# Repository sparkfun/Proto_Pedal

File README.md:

SparkFun Proto Pedal
========================================

[*SparkFun Proto Pedal*](https://www.sparkfun.com/products/13124)

[*SparkFun Proto Pedal Chassis*](https://www.sparkfun.com/products/13967)

The SparkFun Proto Pedal is breatboard featuring prewired I/O boilerplate for building guitar stompboxes.  We also offer a matching predrilled chassis.

_**If you're looking for the Teensy Project Sketches**_ [they're here](https://github.com/sparkfun/Proto_Pedal/tree/master/projects/teensy-based).  Please remember to check the individual sketches for further notes and details in their respective `README.md` files.

Repository Contents
-------------------

* **/Hardware** - Eagle design files (.brd, .sch)
* **/Mechanical** - Enclosure files and related information
* **/Production** - Production panel files (.brd)
* **/Projects** - Example circuits build on the Proto Pedal <PRODUCT NAME>

Documentation
--------------
* **[Proto Pedal Assembly and Theory Guide](https://learn.sparkfun.com/tutorials/proto-pedal-assembly-and-theory-guide)** - Information to help get started.
* **[Chassis Hookup Guide](https://learn.sparkfun.com/tutorials/proto-pedal-chassis-hookup-guide)** - Drilling and painting the enclosure.
* **[Analog Equalizer Project](https://learn.sparkfun.com/tutorials/proto-pedal-example-analog-equalizer-project)** - the gyrator based two-band EQ example.
* **[Teensy-Audio based Programmable Digital Pedal](https://learn.sparkfun.com/tutorials/proto-pedal-example-programmable-digital-pedal)** - building a DSP development platform

Product Versions
----------------
* [SparkFun Proto Pedal](https://www.sparkfun.com/products/13124)
* [SparkFun Proto Pedal Chassis](https://www.sparkfun.com/products/13967)

Version History
---------------
* [441c191](https://github.com/sparkfun/Proto_Pedal/commit/441c1917a6b56c2a821627207be28ff88913c089) - Initial Release

License Information
-------------------

This product is _**open source**_!

Please review the LICENSE.md file for license information.

If you have any questions or concerns on licensing, please contact techsupport@sparkfun.com.

Distributed as-is; no warranty is given.

- Your friends at SparkFun.

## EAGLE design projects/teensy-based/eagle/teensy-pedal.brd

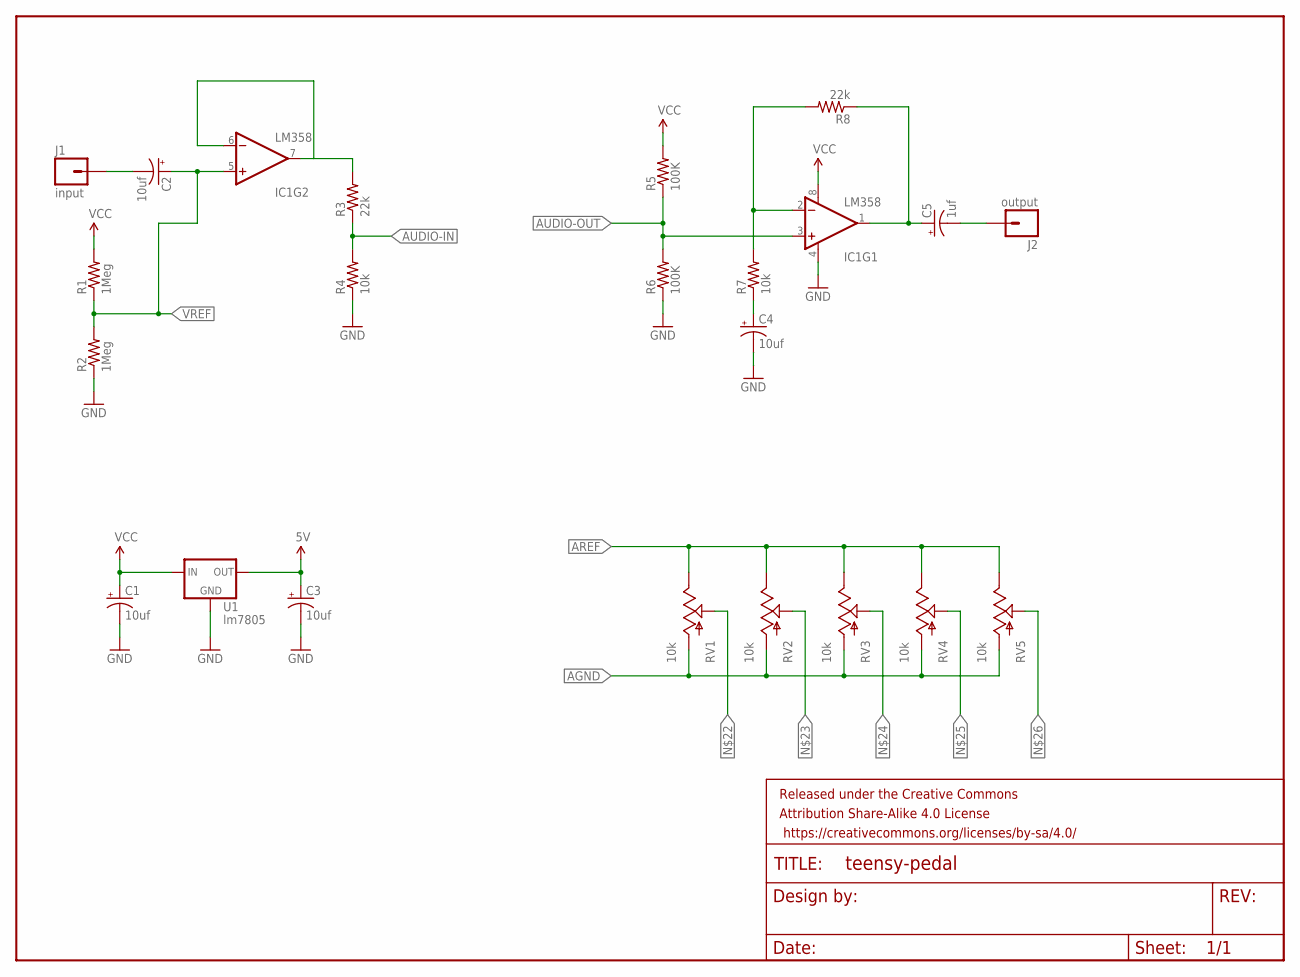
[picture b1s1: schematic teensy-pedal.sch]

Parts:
C1, C2, C3, C4: 10uf; CPOL-RADIAL-10UF-25V
C5: 1uf; CPOL-RADIAL-10UF-25V
FRAME1: FRAME-LETTER; CREATIVE_COMMONS
IC1: LM358; DIP08
J1: input; 1X01NS-KIT
J2: output; 1X01NS-KIT
R1, R2: 1Meg; AXIAL-0.3
R3, R8: 22k; AXIAL-0.3
R4, R7: 10k; AXIAL-0.3
R5, R6: 100K; AXIAL-0.3
RV1, RV2, RV3, RV4, RV5: 10k; POT_ALPHA_RV16AF-20
U1: lm7805; TO-220-ALT

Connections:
5V: C3.1 (+), U1.OUT
AGND: RV1.1 (A), RV2.1 (A), RV3.1 (A), RV4.1 (A), RV5.1 (A)
AREF: RV1.3 (E), RV2.3 (E), RV3.3 (E), RV4.3 (E), RV5.3 (E)
AUDIO-IN: R3.P$1 (1), R4.P$2 (2)
AUDIO-OUT: IC1.3 (+IN), R5.P$1 (1), R6.P$2 (2)
GND: C1.2 (-), C3.2 (-), C4.2 (-), IC1.4 (V-), R2.P$1 (1), R4.P$1 (1), R6.P$1 (1), U1.GND
unnamed: C5.1 (+), IC1.1 (OUT), R8.P$1 (1)
unnamed: IC1.6 (-IN), IC1.7 (OUT), R3.P$2 (2)
unnamed: IC1.2 (-IN), R7.P$2 (2), R8.P$2 (2)
unnamed: C2.2 (-), J1.1
unnamed: C5.2 (-), J2.1
unnamed: C4.1 (+), R7.P$1 (1)
VCC: C1.1 (+), IC1.8 (V+), R1.P$2 (2), R5.P$2 (2), U1.IN
VREF: C2.1 (+), IC1.5 (+IN), R1.P$1 (1), R2.P$2 (2)

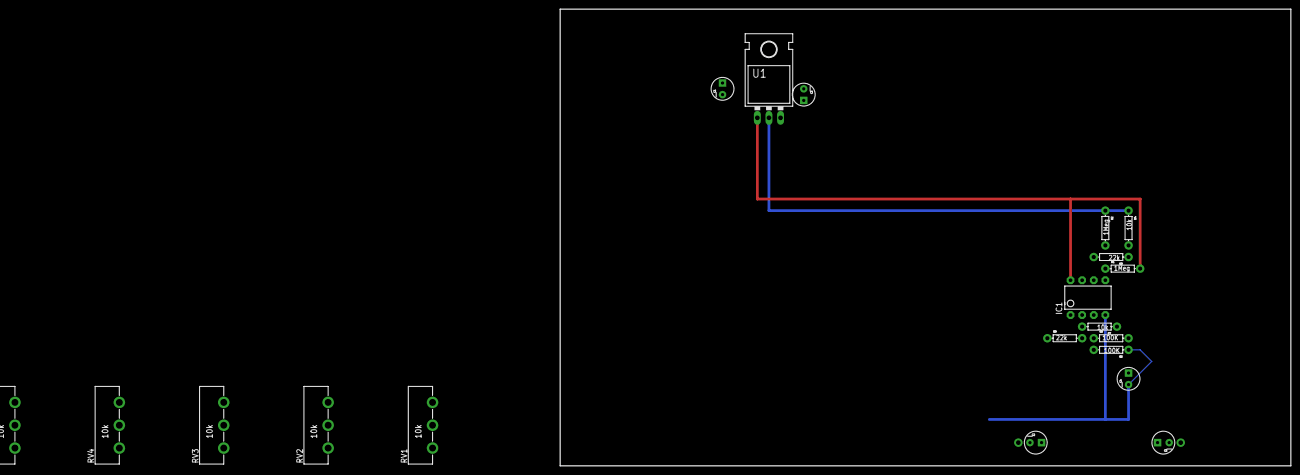
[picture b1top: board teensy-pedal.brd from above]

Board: 2 copper layers, 160.0 x 100.0 mm, 23 parts (0 on the bottom side), 14 nets.

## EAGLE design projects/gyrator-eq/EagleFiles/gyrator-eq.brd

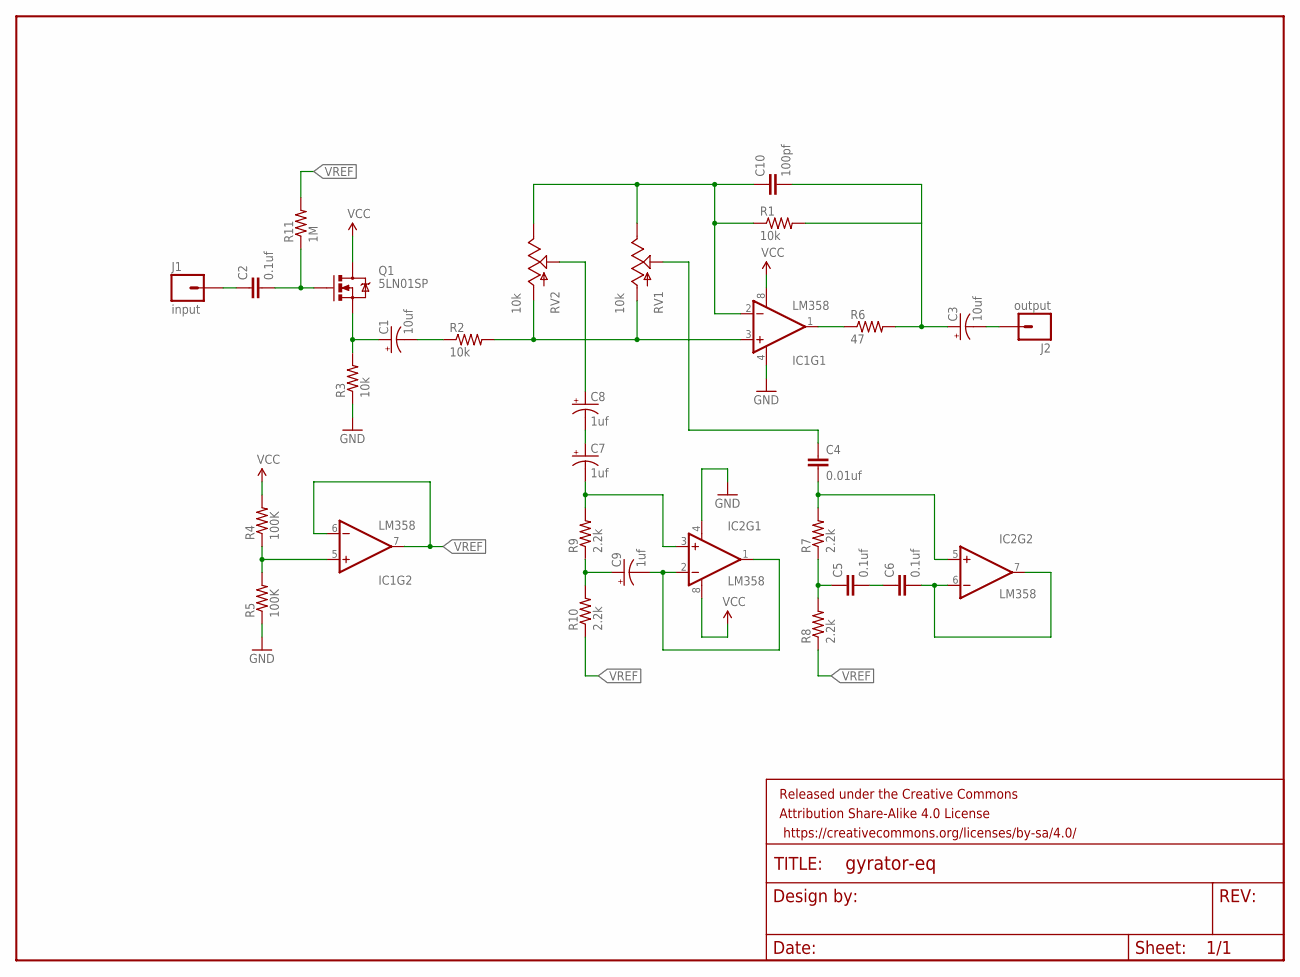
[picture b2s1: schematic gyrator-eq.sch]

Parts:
C1, C3: 10uf; CPOL-RADIAL-10UF-25V
C2: 0.1uf; CAP-PTH-SMALL-KIT
C4: 0.01uf; CAP-PTH-SMALL
C5, C6: 0.1uf; CAP-PTH-SMALL
C7, C8, C9: 1uf; CPOL-RADIAL-10UF-25V
C10: 100pf; CAP-PTH-SMALL
FRAME1: FRAME-LETTER; CREATIVE_COMMONS
IC1, IC2: LM358; DIP08
J1: input; 1X01NS-KIT
J2: output; 1X01NS-KIT
Q1: 5LN01SP; TO-92-AMMO
R1, R2, R3: 10k; AXIAL-0.3
R4, R5: 100K; AXIAL-0.3
R6: 47; AXIAL-0.3
R7, R8, R9, R10: 2.2k; AXIAL-0.3
R11: 1M; AXIAL-0.3
RV1, RV2: 10k; POT_ALPHA_RV16AF-20

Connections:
GND: IC1.4 (V-), IC2.4 (V-), R3.P$1 (1), R5.P$1 (1)
unnamed: C2.2, Q1.3 (G), R11.P$1 (1)
unnamed: C1.1 (+), Q1.1 (S), R3.P$2 (2)
unnamed: C1.2 (-), R2.P$1 (1)
unnamed: IC1.3 (+IN), R2.P$2 (2), RV1.1 (A), RV2.1 (A)
unnamed: IC1.1 (OUT), R6.P$1 (1)
unnamed: C3.1 (+), C10.2, R1.P$2 (2), R6.P$2 (2)
unnamed: C10.1, IC1.2 (-IN), R1.P$1 (1), RV1.3 (E), RV2.3 (E)
unnamed: IC1.5 (+IN), R4.P$1 (1), R5.P$2 (2)
unnamed: C2.1, J1.1
unnamed: C8.1 (+), RV2.2 (S)
unnamed: C7.1 (+), C8.2 (-)
unnamed: C7.2 (-), IC2.3 (+IN), R9.P$2 (2)
unnamed: C9.1 (+), R9.P$1 (1), R10.P$2 (2)
unnamed: C4.1, RV1.2 (S)
unnamed: C6.2, IC2.6 (-IN), IC2.7 (OUT)
unnamed: C9.2 (-), IC2.1 (OUT), IC2.2 (-IN)
unnamed: C4.2, IC2.5 (+IN), R7.P$2 (2)
unnamed: C5.2, C6.1
unnamed: C5.1, R7.P$1 (1), R8.P$2 (2)
unnamed: C3.2 (-), J2.1
VCC: IC1.8 (V+), IC2.8 (V+), Q1.2 (D), R4.P$2 (2)
VREF: IC1.6 (-IN), IC1.7 (OUT), R8.P$1 (1), R10.P$1 (1), R11.P$2 (2)

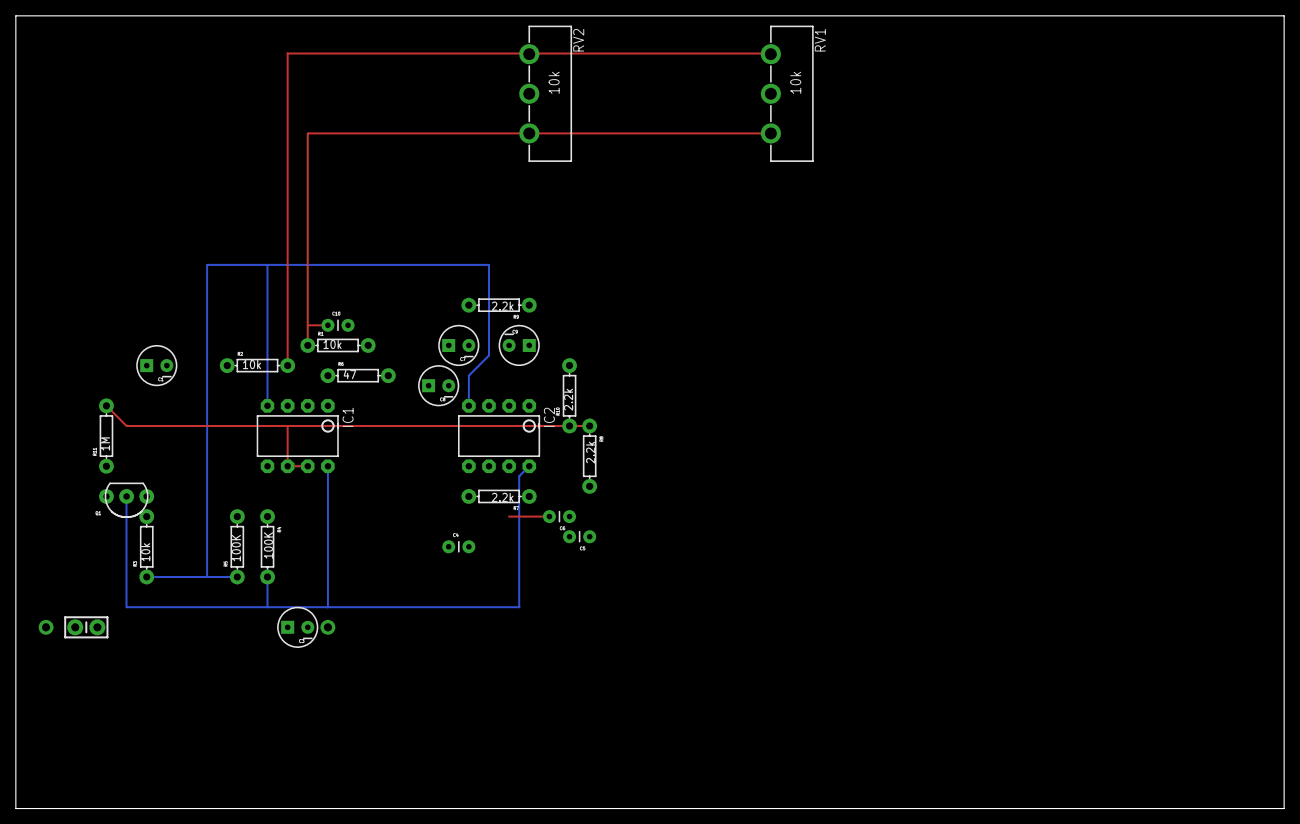
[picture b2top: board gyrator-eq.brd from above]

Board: 2 copper layers, 160.0 x 100.0 mm, 29 parts (0 on the bottom side), 23 nets.

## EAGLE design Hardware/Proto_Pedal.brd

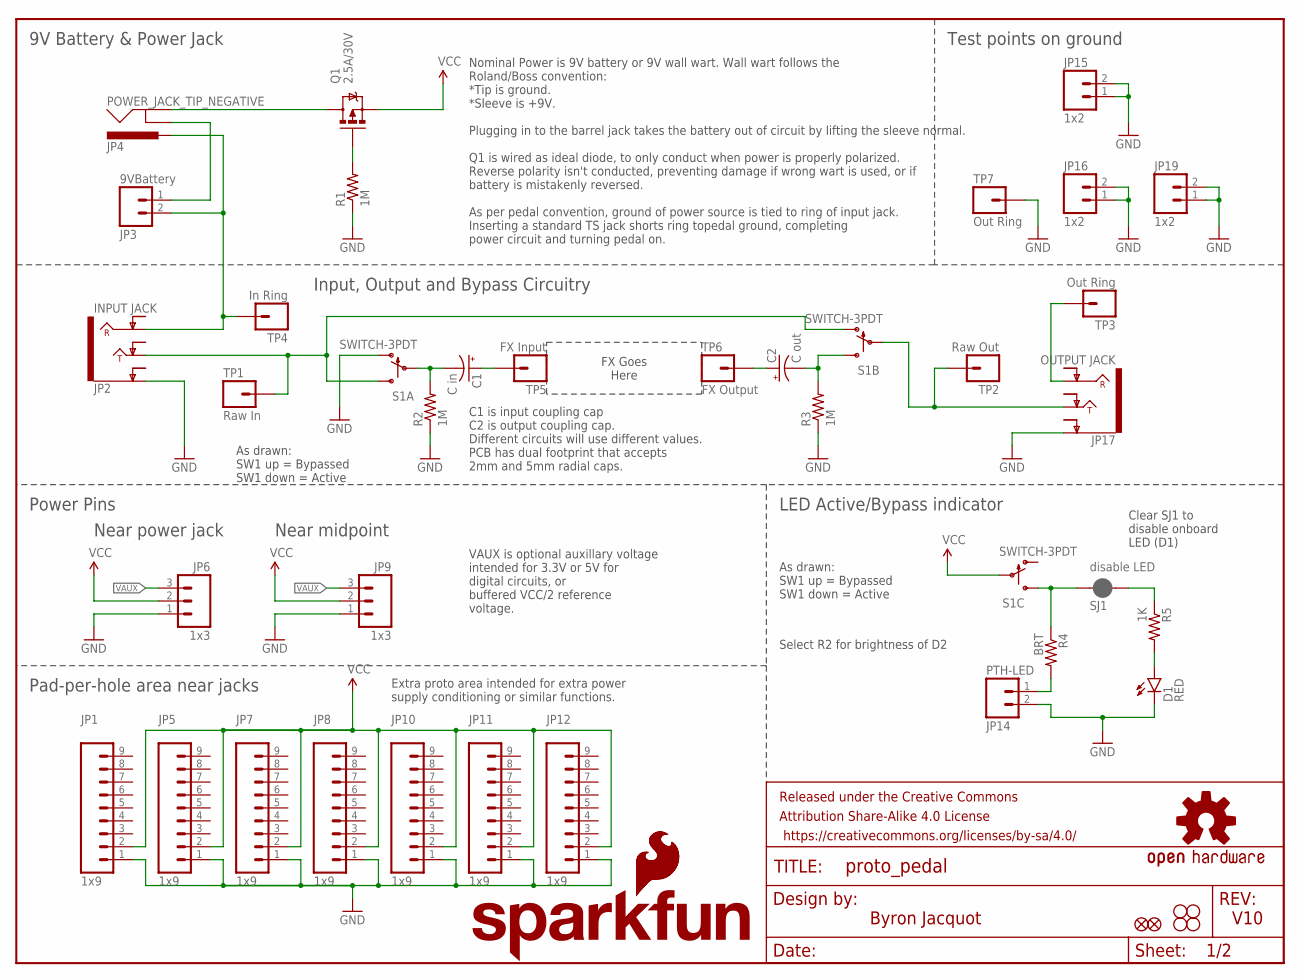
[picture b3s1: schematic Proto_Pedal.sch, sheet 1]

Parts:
C1: C in; DUAL-CAP
C2: C out; DUAL-CAP
D1: RED; LED-0603
FID1, FID2: FIDUCIAL1X2; FIDUCIAL-1X2
FRAME1: FRAME-LETTER; CREATIVE_COMMONS
JP1, JP5, JP7, JP8, JP10, JP11, JP12: 1x9; 1X09_NO_SILK
JP2: INPUT JACK; AUDIO-JACK-.25-INCH-HORIZ-PTH
JP3: 9VBattery; 1X02_LONGPADS
JP4: POWER_JACK_TIP_NEGATIVE; POWER-BARRELJACK-PTH-LOCK-FIXED
JP6, JP9: 1x3; 1X03_NO_SILK
JP14: PTH-LED; 1X02_LONGPADS
JP15, JP16, JP19: 1x2; 1X02_NO_SILK
JP17: OUTPUT JACK; AUDIO-JACK-.25-INCH-HORIZ-PTH
LOGO1: SFE_LOGO_NAME_FLAME.2_INCH; SFE_LOGO_NAME_FLAME_.2
LOGO2: OSHW-LOGOL; OSHW-LOGO-L
LOGO3: SFE_LOGO_FLAME.2_INCH; SFE_LOGO_FLAME_.2
Q1: 2.5A/30V; SOT23-3
R1, R2, R3: 1M; 0603-RES
R4: BRT; AXIAL-0.3
R5: 1K; 0603-RES
S1: SWITCH-3PDT; STOMP-SWITCH-3PDT
SJ1: disable LED; PAD-JUMPER-2-NC_BY_PASTE_YES_SILK_FULL_BOX
STANDOFF1, STANDOFF2, STANDOFF3, STANDOFF4: STAND-OFF
TP1: Raw In; 1X01_NO_SILK
TP2: Raw Out; 1X01_NO_SILK
TP3: Out Ring; 1X01_NO_SILK
TP4: In Ring; 1X01_NO_SILK
TP5: FX Input; 1X01_NO_SILK
TP6: FX Output; 1X01_NO_SILK
TP7: Out Ring; 1X01_LONGPAD

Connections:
FX_IN: C1.P$2 (-), C1.P$3 (-), R2.2, S1.P$2
FX_OUT: C2.P$2 (-), C2.P$3 (-), R3.2, S1.P$6 (S)
GND: D1.C, JP1.1, JP2.SLEEVE (EARTH), JP5.1, JP6.1, JP7.1, JP8.1, JP9.1, JP10.1, JP11.1, JP12.1, JP14.2, JP15.1, JP15.2, JP16.1, JP16.2, JP17.SLEEVE (EARTH), JP19.1, JP19.2, R1.1, R2.1, R3.1, S1.P$1 (O), TP7.1; also elsewhere on the board
LEDA: JP14.1, R4.P$2 (2)
unnamed: D1.A, R5.2
unnamed: R4.P$1 (1), S1.P$9 (S), SJ1.1
unnamed: JP3.1, JP4.SLEEVE-NORMAL (SLEEVEBREAK)
unnamed: JP2.RING, JP3.2, JP4.TIP, TP4.1
unnamed: R5.1, SJ1.2
unnamed: JP17.RING, TP3.1
unnamed: C1.P$1 (+), TP5.1
unnamed: C2.P$1 (+), TP6.1
unnamed: JP2.TIP, S1.P$3 (S), S1.P$4 (O), TP1.1
unnamed: JP17.TIP, S1.P$5, TP2.1
unnamed: Q1.1 (G), R1.2
VAUX: JP6.3, JP9.3
VBATT: JP4.SLEEVE, Q1.3 (D)
VCC: JP1.2, JP5.2, JP6.2, JP7.2, JP8.2, JP9.2, JP10.2, JP11.2, JP12.2, Q1.2 (S), S1.P$8; also elsewhere on the board

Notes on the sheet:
Byron Jacquot
V10
Power Pins
Near midpoint
Clear SJ1 to disable onboard LED (D1)
As drawn: SW1 up = Bypassed SW1 down = Active
Test points on ground
FX Goes Here
9V Battery & Power Jack
Input, Output and Bypass Circuitry
Near power jack
LED Active/Bypass indicator
Pad-per-hole area near jacks
Nominal Power is 9V battery or 9V wall wart. Wall wart follows the Roland/Boss convention: *Tip is ground. *Sleeve is +9V. Plugging in to the barrel jack takes the battery out of circuit by lifting the sleeve normal. Q1 is wired as ideal diode, to only conduct when power is properly polarized. Reve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
VAUX is optional auxillary voltage intended for 3.3V or 5V for digital circuits, or buffered VCC/2 reference voltage.
Extra proto area intended for extra power supply conditioning or similar functions.
C1 is input coupling cap C2 is output coupling cap. Different circuits will use different values. PCB has dual footprint that accepts 2mm and 5mm radial caps.
Select R2 for brightness of D2

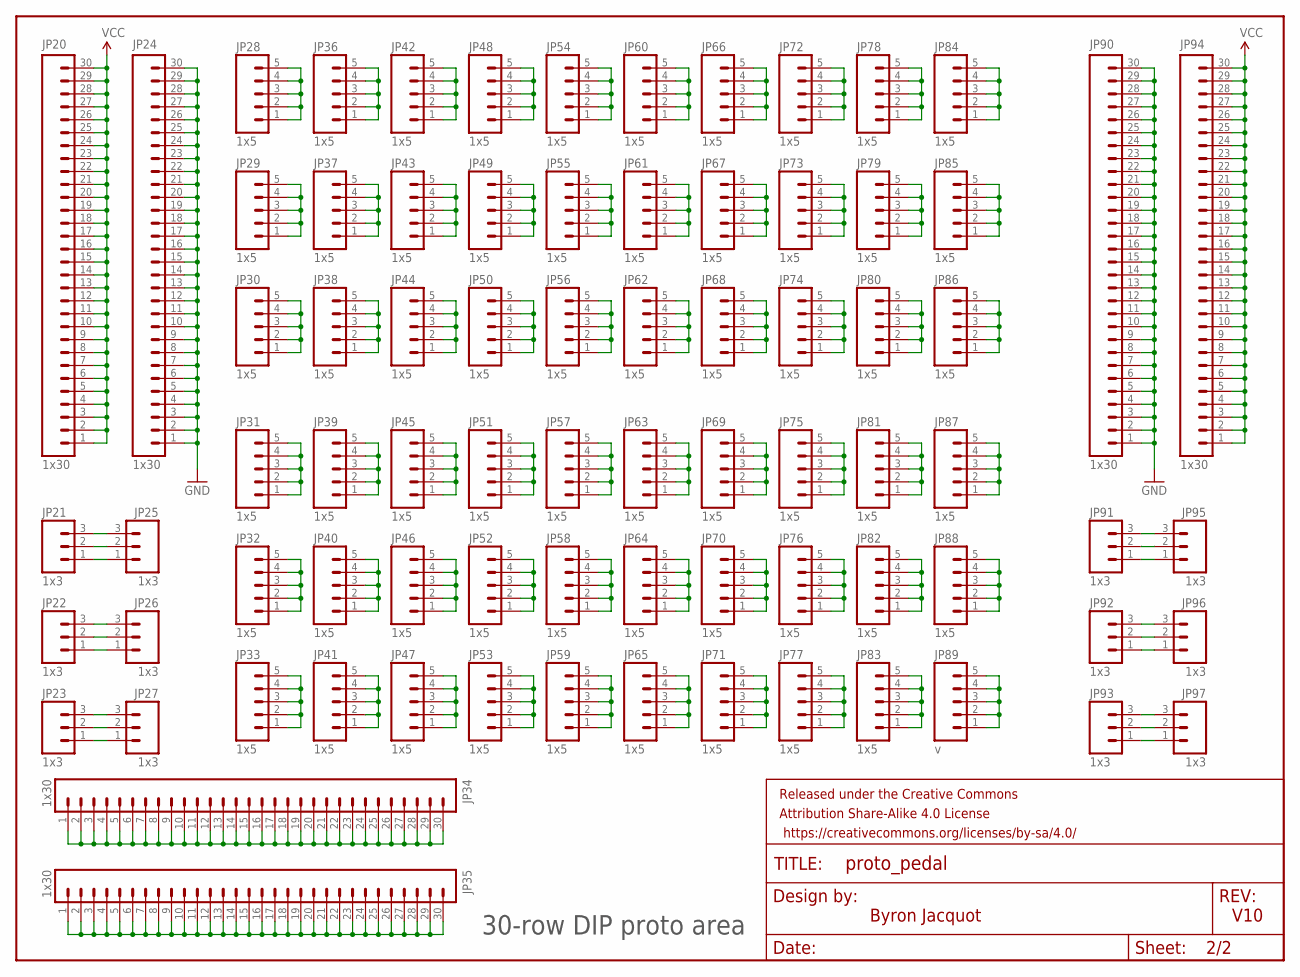
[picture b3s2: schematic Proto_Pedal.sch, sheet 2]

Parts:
FRAME2: FRAME-LETTER; CREATIVE_COMMONS
JP20, JP24, JP34, JP35, JP90, JP94: 1x30; 1X30_NO_SILK
JP21, JP22, JP23, JP25, JP26, JP27, JP91, JP92, JP93, JP95, JP96, JP97: 1x3; 1X03_NO_SILK
JP28, JP29, JP30, JP31, JP32, JP33, JP36, JP37, JP38, JP39, JP40, JP41, JP42, JP43, JP44, JP45, JP46, JP47, JP48, JP49, JP50, JP51, JP52, JP53, JP54, JP55, JP56, JP57, JP58, JP59, JP60, JP61, JP62, JP63, JP64, JP65, JP66, JP67, JP68, JP69, JP70, JP71, JP72, JP73, JP74, JP75, JP76, JP77, JP78, JP79, JP80, JP81, JP82, JP83, JP84, JP85, JP86, JP87, JP88: 1x5; 1X05_NO_SILK
JP89: v; 1X05_NO_SILK

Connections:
GND: JP24.1, JP24.2, JP24.3, JP24.4, JP24.5, JP24.6, JP24.7, JP24.8, JP24.9, JP24.10, JP24.11, JP24.12, JP24.13, JP24.14, JP24.15, JP24.16, JP24.17, JP24.18, JP24.19, JP24.20, JP24.21, JP24.22, JP24.23, JP24.24, JP24.25, JP24.26, JP24.27, JP24.28, JP24.29, JP24.30, JP90.1, JP90.2, JP90.3, JP90.4, JP90.5, JP90.6, JP90.7, JP90.8, JP90.9, JP90.10, JP90.11, JP90.12, JP90.13, JP90.14, JP90.15, JP90.16, JP90.17, JP90.18, JP90.19, JP90.20, JP90.21, JP90.22, JP90.23, JP90.24, JP90.25, JP90.26, JP90.27, JP90.28, JP90.29, JP90.30; also elsewhere on the board
unnamed: JP84.1, JP84.2, JP84.3, JP84.4, JP84.5
unnamed: JP85.1, JP85.2, JP85.3, JP85.4, JP85.5
unnamed: JP86.1, JP86.2, JP86.3, JP86.4, JP86.5
unnamed: JP87.1, JP87.2, JP87.3, JP87.4, JP87.5
unnamed: JP54.1, JP54.2, JP54.3, JP54.4, JP54.5
unnamed: JP88.1, JP88.2, JP88.3, JP88.4, JP88.5
unnamed: JP78.1, JP78.2, JP78.3, JP78.4, JP78.5
unnamed: JP72.1, JP72.2, JP72.3, JP72.4, JP72.5
unnamed: JP66.1, JP66.2, JP66.3, JP66.4, JP66.5
unnamed: JP60.1, JP60.2, JP60.3, JP60.4, JP60.5
unnamed: JP48.1, JP48.2, JP48.3, JP48.4, JP48.5
unnamed: JP42.1, JP42.2, JP42.3, JP42.4, JP42.5
unnamed: JP36.1, JP36.2, JP36.3, JP36.4, JP36.5
unnamed: JP28.1, JP28.2, JP28.3, JP28.4, JP28.5
unnamed: JP89.1, JP89.2, JP89.3, JP89.4, JP89.5
unnamed: JP79.1, JP79.2, JP79.3, JP79.4, JP79.5
unnamed: JP73.1, JP73.2, JP73.3, JP73.4, JP73.5
unnamed: JP67.1, JP67.2, JP67.3, JP67.4, JP67.5
unnamed: JP61.1, JP61.2, JP61.3, JP61.4, JP61.5
unnamed: JP55.1, JP55.2, JP55.3, JP55.4, JP55.5
unnamed: JP49.1, JP49.2, JP49.3, JP49.4, JP49.5
unnamed: JP43.1, JP43.2, JP43.3, JP43.4, JP43.5
unnamed: JP37.1, JP37.2, JP37.3, JP37.4, JP37.5
unnamed: JP29.1, JP29.2, JP29.3, JP29.4, JP29.5
unnamed: JP80.1, JP80.2, JP80.3, JP80.4, JP80.5
unnamed: JP74.1, JP74.2, JP74.3, JP74.4, JP74.5
unnamed: JP68.1, JP68.2, JP68.3, JP68.4, JP68.5
unnamed: JP62.1, JP62.2, JP62.3, JP62.4, JP62.5
unnamed: JP56.1, JP56.2, JP56.3, JP56.4, JP56.5
unnamed: JP50.1, JP50.2, JP50.3, JP50.4, JP50.5
unnamed: JP44.1, JP44.2, JP44.3, JP44.4, JP44.5
unnamed: JP38.1, JP38.2, JP38.3, JP38.4, JP38.5
unnamed: JP30.1, JP30.2, JP30.3, JP30.4, JP30.5
unnamed: JP81.1, JP81.2, JP81.3, JP81.4, JP81.5
unnamed: JP75.1, JP75.2, JP75.3, JP75.4, JP75.5
unnamed: JP69.1, JP69.2, JP69.3, JP69.4, JP69.5
unnamed: JP63.1, JP63.2, JP63.3, JP63.4, JP63.5
unnamed: JP57.1, JP57.2, JP57.3, JP57.4, JP57.5
unnamed: JP51.1, JP51.2, JP51.3, JP51.4, JP51.5
unnamed: JP45.1, JP45.2, JP45.3, JP45.4, JP45.5
unnamed: JP39.1, JP39.2, JP39.3, JP39.4, JP39.5
unnamed: JP31.1, JP31.2, JP31.3, JP31.4, JP31.5
unnamed: JP82.1, JP82.2, JP82.3, JP82.4, JP82.5
unnamed: JP76.1, JP76.2, JP76.3, JP76.4, JP76.5
unnamed: JP70.1, JP70.2, JP70.3, JP70.4, JP70.5
unnamed: JP64.1, JP64.2, JP64.3, JP64.4, JP64.5
unnamed: JP58.1, JP58.2, JP58.3, JP58.4, JP58.5
unnamed: JP52.1, JP52.2, JP52.3, JP52.4, JP52.5
unnamed: JP46.1, JP46.2, JP46.3, JP46.4, JP46.5
unnamed: JP40.1, JP40.2, JP40.3, JP40.4, JP40.5
unnamed: JP32.1, JP32.2, JP32.3, JP32.4, JP32.5
unnamed: JP83.1, JP83.2, JP83.3, JP83.4, JP83.5
unnamed: JP77.1, JP77.2, JP77.3, JP77.4, JP77.5
unnamed: JP71.1, JP71.2, JP71.3, JP71.4, JP71.5
unnamed: JP65.1, JP65.2, JP65.3, JP65.4, JP65.5
unnamed: JP59.1, JP59.2, JP59.3, JP59.4, JP59.5
unnamed: JP53.1, JP53.2, JP53.3, JP53.4, JP53.5
unnamed: JP47.1, JP47.2, JP47.3, JP47.4, JP47.5
unnamed: JP41.1, JP41.2, JP41.3, JP41.4, JP41.5
unnamed: JP33.1, JP33.2, JP33.3, JP33.4, JP33.5
unnamed: JP21.1, JP25.1
unnamed: JP21.2, JP25.2
unnamed: JP21.3, JP25.3
unnamed: JP22.1, JP26.1
unnamed: JP22.2, JP26.2
unnamed: JP22.3, JP26.3
unnamed: JP34.1, JP34.2, JP34.3, JP34.4, JP34.5, JP34.6, JP34.7, JP34.8, JP34.9, JP34.10, JP34.11, JP34.12, JP34.13, JP34.14, JP34.15, JP34.16, JP34.17, JP34.18, JP34.19, JP34.20, JP34.21, JP34.22, JP34.23, JP34.24, JP34.25, JP34.26, JP34.27, JP34.28, JP34.29, JP34.30
unnamed: JP35.1, JP35.2, JP35.3, JP35.4, JP35.5, JP35.6, JP35.7, JP35.8, JP35.9, JP35.10, JP35.11, JP35.12, JP35.13, JP35.14, JP35.15, JP35.16, JP35.17, JP35.18, JP35.19, JP35.20, JP35.21, JP35.22, JP35.23, JP35.24, JP35.25, JP35.26, JP35.27, JP35.28, JP35.29, JP35.30
unnamed: JP23.1, JP27.1
unnamed: JP23.2, JP27.2
unnamed: JP23.3, JP27.3
unnamed: JP91.1, JP95.1
unnamed: JP91.2, JP95.2
unnamed: JP91.3, JP95.3
unnamed: JP92.1, JP96.1
unnamed: JP92.2, JP96.2
unnamed: JP92.3, JP96.3
unnamed: JP93.1, JP97.1
unnamed: JP93.2, JP97.2
unnamed: JP93.3, JP97.3
VCC: JP20.1, JP20.2, JP20.3, JP20.4, JP20.5, JP20.6, JP20.7, JP20.8, JP20.9, JP20.10, JP20.11, JP20.12, JP20.13, JP20.14, JP20.15, JP20.16, JP20.17, JP20.18, JP20.19, JP20.20, JP20.21, JP20.22, JP20.23, JP20.24, JP20.25, JP20.26, JP20.27, JP20.28, JP20.29, JP20.30, JP94.1, JP94.2, JP94.3, JP94.4, JP94.5, JP94.6, JP94.7, JP94.8, JP94.9, JP94.10, JP94.11, JP94.12, JP94.13, JP94.14, JP94.15, JP94.16, JP94.17, JP94.18, JP94.19, JP94.20, JP94.21, JP94.22, JP94.23, JP94.24, JP94.25, JP94.26, JP94.27, JP94.28, JP94.29, JP94.30; also elsewhere on the board

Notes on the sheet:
Byron Jacquot
V10
30-row DIP proto area

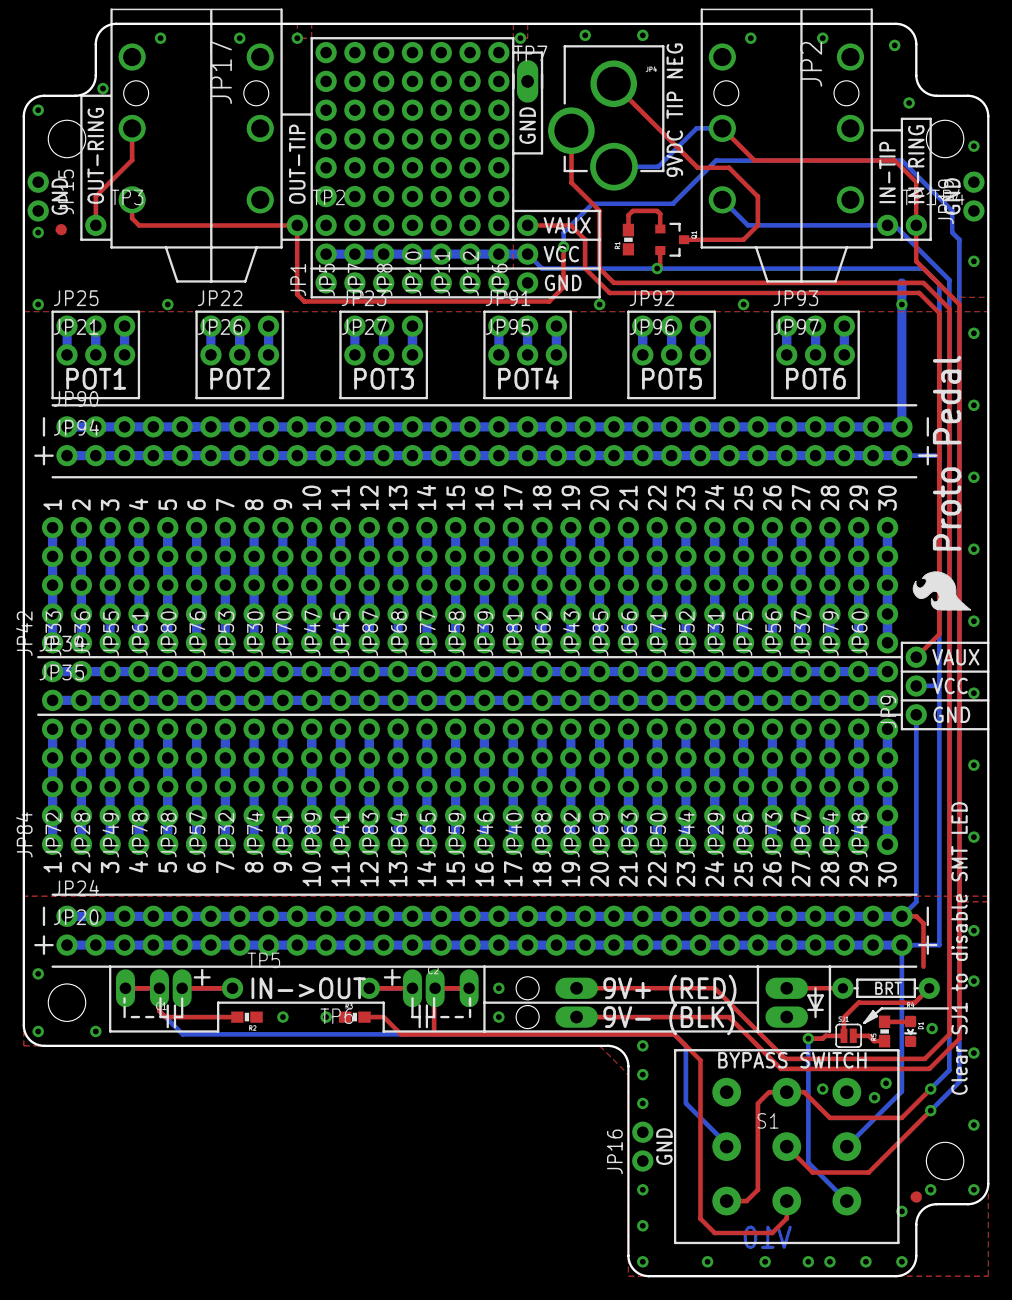
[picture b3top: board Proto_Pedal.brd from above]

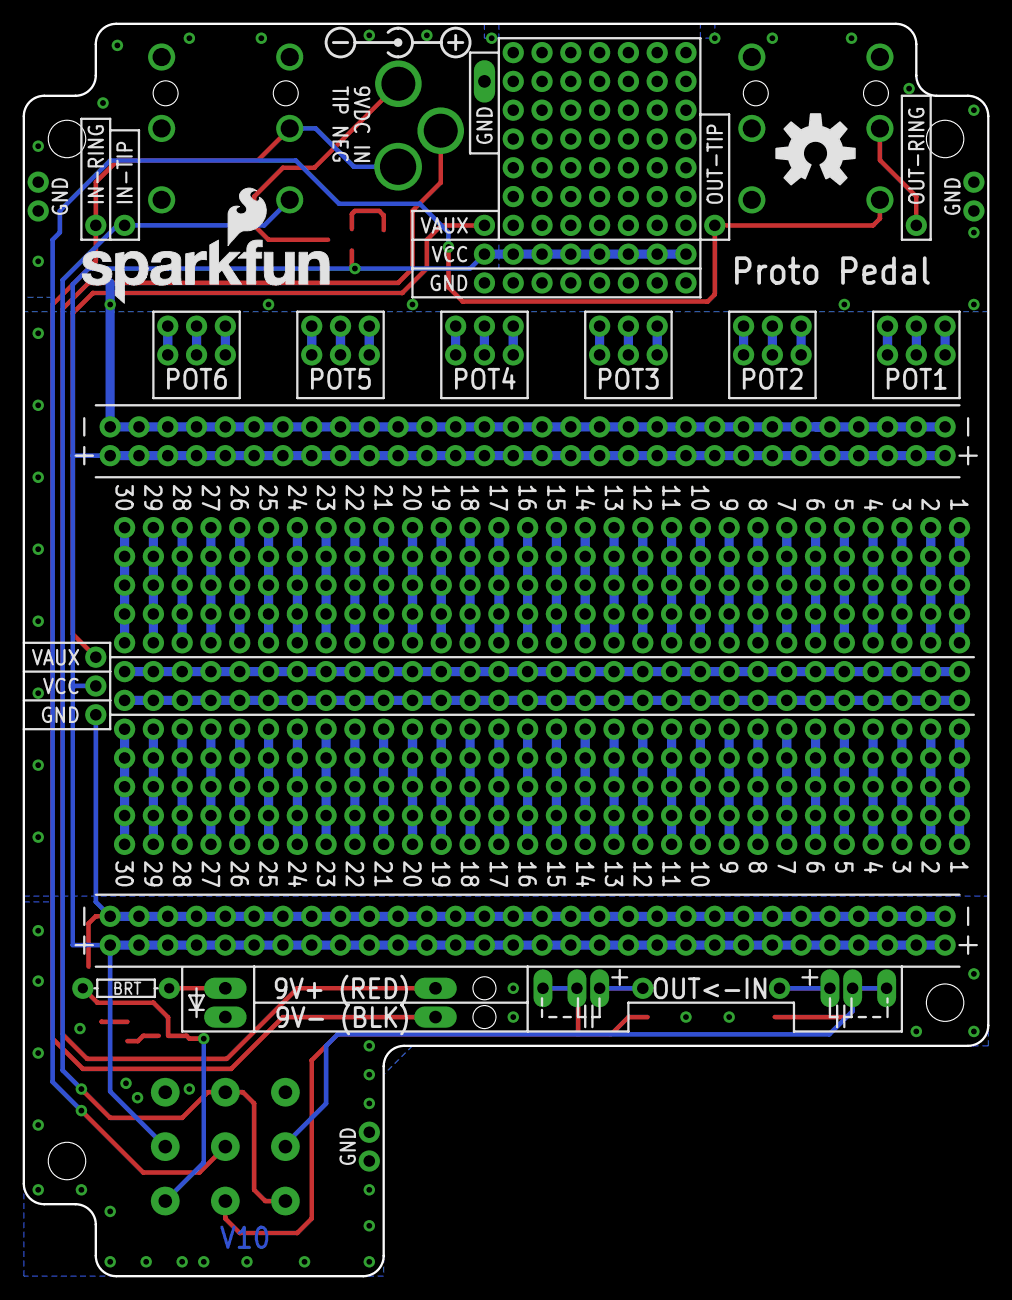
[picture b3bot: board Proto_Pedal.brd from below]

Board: 2 copper layers, 85.1 x 110.5 mm, 124 parts (3 on the bottom side), 98 nets.

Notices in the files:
parts and their libraries:
SparkFun-Aesthetics: Licensing: Creative Commons ShareAlike 4.0 International - https://creativecommons.org/licenses/by-sa/4.0
SparkFun-Aesthetics: Released under the Creative Commons Attribution Share-Alike 4.0 License
SparkFun-Aesthetics: https://creativecommons.org/licenses/by-sa/4.0
